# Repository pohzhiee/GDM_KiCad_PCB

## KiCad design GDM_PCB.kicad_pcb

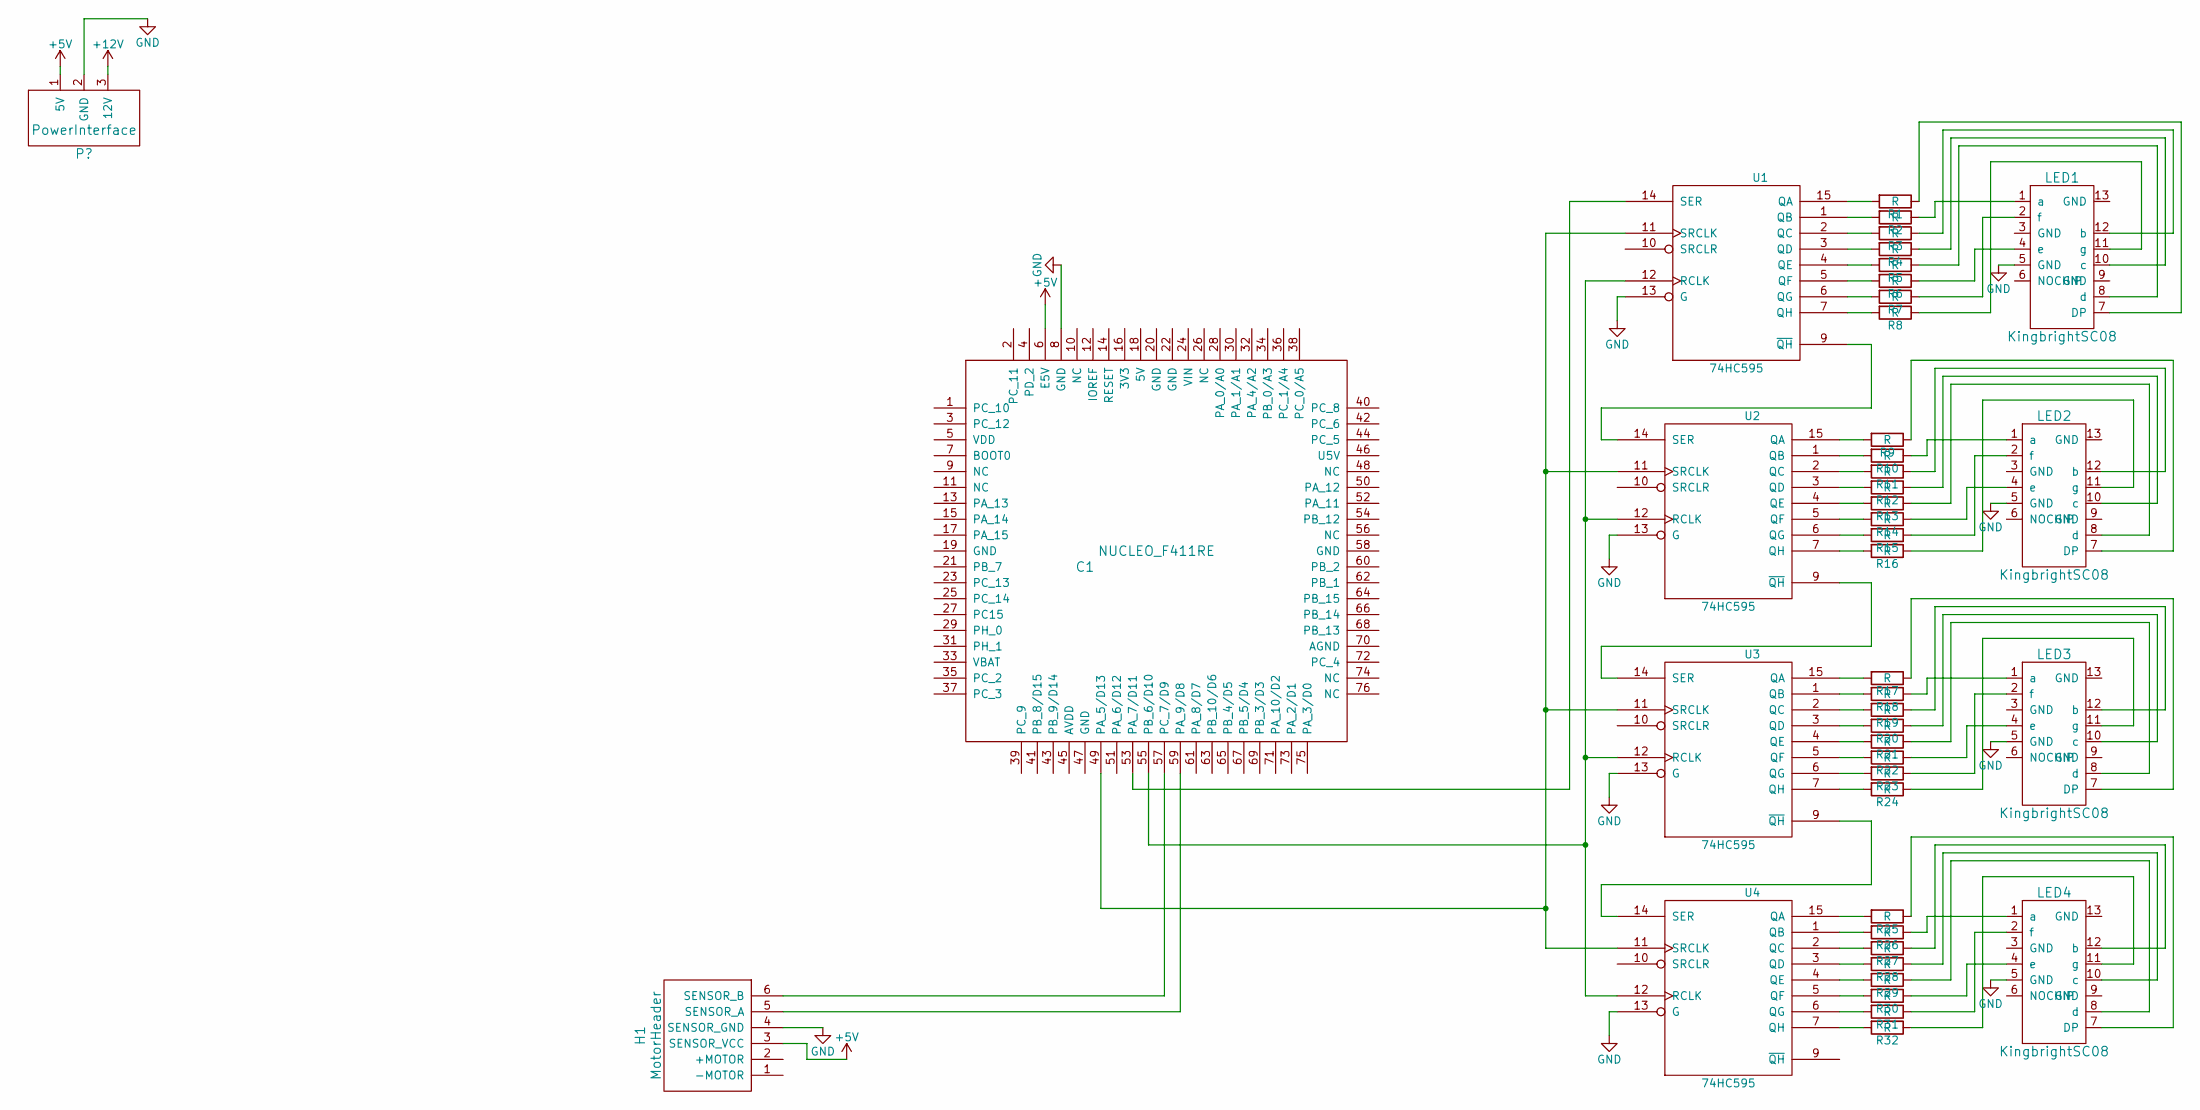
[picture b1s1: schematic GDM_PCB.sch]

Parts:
C1: NUCLEO_F411RE; NUCLEO_F411RE_MORPHO
H1: MotorHeader
LED1, LED2, LED3, LED4: KingbrightSC08; kingbrightSC08
R1, R2, R3, R4, R5, R6, R7, R8, R9, R10, R11, R12, R13, R14, R15, R16, R17, R18, R19, R20, R21, R22, R23, R24, R25, R26, R27, R28, R29, R30, R31, R32: R; Resistor
U1, U2, U3, U4: 74HC595; 74HC595N

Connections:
GND: C1.8 (GND), H1.4 (SENSOR_GND), LED1.5 (GND), LED2.5 (GND), LED3.5 (GND), LED4.5 (GND), U1.8 (GND), U1.13 (G), U2.8 (GND), U2.13 (G), U3.8 (GND), U3.13 (G), U4.8 (GND), U4.13 (G)
unnamed: C1.49 (PA_5/D13), U1.11 (SRCLK), U2.11 (SRCLK), U3.11 (SRCLK), U4.11 (SRCLK)
unnamed: C1.53 (PA_7/D11), U1.14 (SER)
unnamed: C1.55 (PB_6/D10), U1.12 (RCLK), U2.12 (RCLK), U3.12 (RCLK), U4.12 (RCLK)
unnamed: C1.6 (E5V), H1.3 (SENSOR_VCC)
unnamed: C1.59 (PA_9/D8), H1.5 (SENSOR_A)
unnamed: C1.57 (PC_7/D9), H1.6 (SENSOR_B)
unnamed: LED1.1 (a), R2.1
unnamed: LED1.2 (f), R7.1
unnamed: LED1.4 (e), R6.1
unnamed: LED1.7 (DP), R1.1
unnamed: LED1.8 (d), R5.1
unnamed: LED1.10 (c), R4.1
unnamed: LED1.11 (g), R8.1
unnamed: LED1.12 (b), R3.1
unnamed: LED2.1 (a), R10.1
unnamed: LED2.2 (f), R15.1
unnamed: LED2.4 (e), R14.1
unnamed: LED2.7 (DP), R9.1
unnamed: LED2.8 (d), R13.1
unnamed: LED2.10 (c), R12.1
unnamed: LED2.11 (g), R16.1
unnamed: LED2.12 (b), R11.1
unnamed: LED3.1 (a), R18.1
unnamed: LED3.2 (f), R23.1
unnamed: LED3.4 (e), R22.1
unnamed: LED3.7 (DP), R17.1
unnamed: LED3.8 (d), R21.1
unnamed: LED3.10 (c), R20.1
unnamed: LED3.11 (g), R24.1
unnamed: LED3.12 (b), R19.1
unnamed: LED4.1 (a), R26.1
unnamed: LED4.2 (f), R31.1
unnamed: LED4.4 (e), R30.1
unnamed: LED4.7 (DP), R25.1
unnamed: LED4.8 (d), R29.1
unnamed: LED4.10 (c), R28.1
unnamed: LED4.11 (g), R32.1
unnamed: LED4.12 (b), R27.1
unnamed: R1.2, U1.15 (QA)
unnamed: R2.2, U1.1 (QB)
unnamed: R3.2, U1.2 (QC)
unnamed: R4.2, U1.3 (QD)
unnamed: R5.2, U1.4 (QE)
unnamed: R6.2, U1.5 (QF)
unnamed: R7.2, U1.6 (QG)
unnamed: R8.2, U1.7 (QH)
unnamed: R9.2, U2.15 (QA)
unnamed: R10.2, U2.1 (QB)
unnamed: R11.2, U2.2 (QC)
unnamed: R12.2, U2.3 (QD)
unnamed: R13.2, U2.4 (QE)
unnamed: R14.2, U2.5 (QF)
unnamed: R15.2, U2.6 (QG)
unnamed: R16.2, U2.7 (QH)
unnamed: R17.2, U3.15 (QA)
unnamed: R18.2, U3.1 (QB)
unnamed: R19.2, U3.2 (QC)
unnamed: R20.2, U3.3 (QD)
unnamed: R21.2, U3.4 (QE)
unnamed: R22.2, U3.5 (QF)
unnamed: R23.2, U3.6 (QG)
unnamed: R24.2, U3.7 (QH)
unnamed: R25.2, U4.15 (QA)
unnamed: R26.2, U4.1 (QB)
unnamed: R27.2, U4.2 (QC)
unnamed: R28.2, U4.3 (QD)
unnamed: R29.2, U4.4 (QE)
unnamed: R30.2, U4.5 (QF)
unnamed: R31.2, U4.6 (QG)
unnamed: R32.2, U4.7 (QH)
unnamed: U1.9 (~QH), U2.14 (SER)
unnamed: U2.9 (~QH), U3.14 (SER)
unnamed: U3.9 (~QH), U4.14 (SER)
VCC: U1.16 (VCC), U2.16 (VCC), U3.16 (VCC), U4.16 (VCC)

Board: 2 copper layers, 41 parts (0 on the bottom side), 72 nets, no tracks yet.

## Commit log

2018-03-15 some change
    blah
2018-03-15 added stm32 and completed connection to 74hc595 and 7seg with resistors
2018-03-16 completed nucleo f411re morpho connector footprint + library
2018-03-16 completed kingbrightSC08 footprint (redo)
2018-03-16 added resistor footprint
2018-03-16 finished footprints, connections, and PCB arrangement for 7seg setup
